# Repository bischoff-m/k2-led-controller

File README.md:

# LED Controller for K2 Bar
This app is composed of an electron app and an arduino file. The arduino controls LEDs via a custom DMX protocol and the electron app lets the user control the color and brightness of the LEDs. This application is specifically built for K2 Bar.

# Arduino Controller
Using a modified version of DmxSimple:
https://github.com/PaulStoffregen/DmxSimple

# Electron App
Use yarn instead of npm

To use electron-rebuild, setup your Visual Studio version via 
```
yarn run node-gyp configure --msvs_version=2017
```
or
```
npm config edit
```

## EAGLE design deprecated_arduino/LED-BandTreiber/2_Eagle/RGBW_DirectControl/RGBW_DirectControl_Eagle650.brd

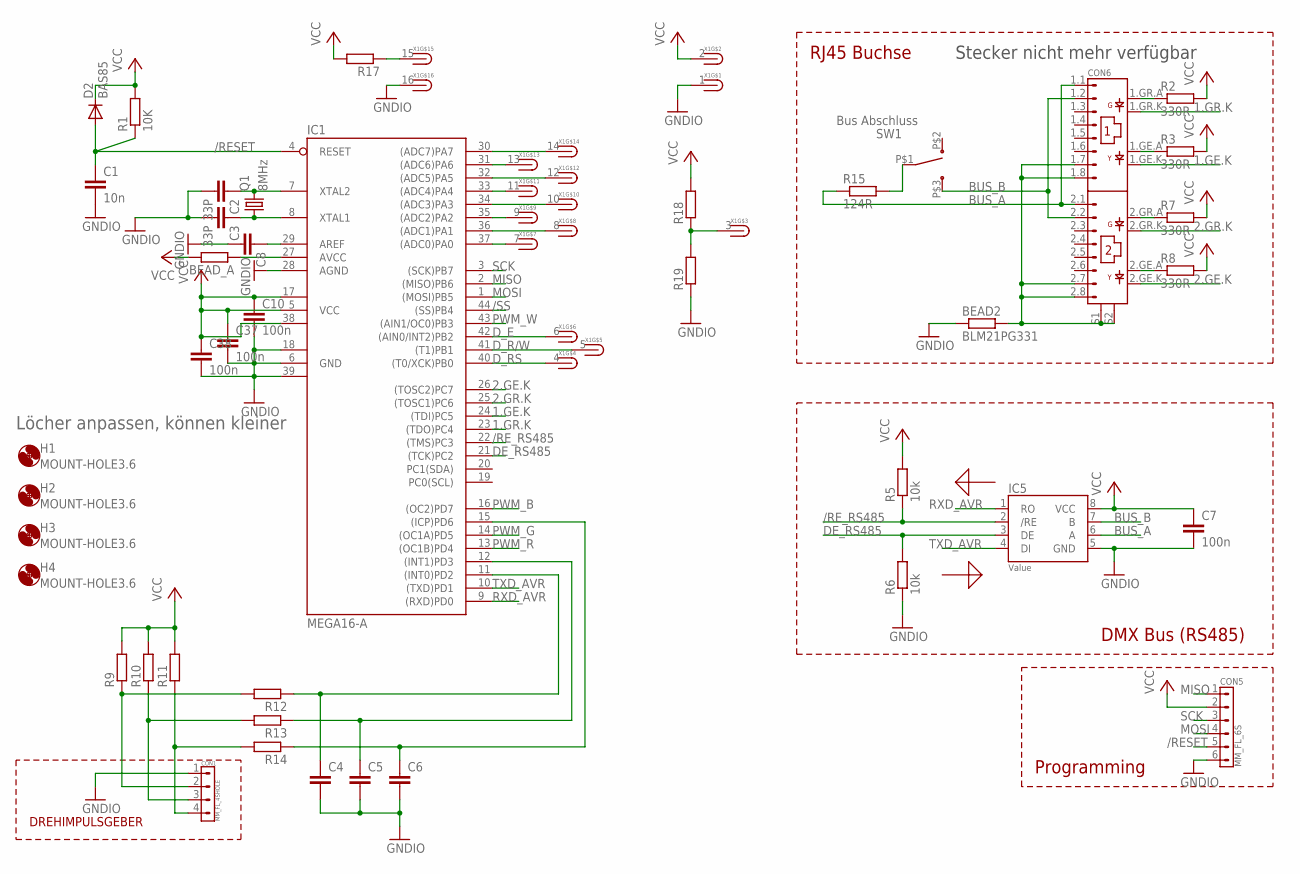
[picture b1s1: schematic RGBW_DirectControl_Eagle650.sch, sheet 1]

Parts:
BEAD2: BLM21PG331; R0805
BEAD_A: R-EU_R0805; R0805
C1: 10n; C0805
C2, C3: 33P; C0805
C4, C5, C6, C8: C-EUC0805; C0805
C7, C10, C37, C38: 100n; C0805
CON1: MM_FL_4SHOLE; MM_FL_4G
CON5: MM_FL_6S; MM_FL_6G
CON6: RJ45_2ER_LED
D2: BAS85; SOD80C
H1, H2, H3, H4: MOUNT-HOLE3.6; 3,6
IC1: MEGA16-A; TQFP44
IC5: LT1785; SO08
Q1: 8MHz; HC49/S
R1: 10K; R0805
R2, R3, R7, R8: 330R; R0805
R5, R6: 10k; R0805
R9, R10, R11, R12, R13, R14, R18, R19: R-EU_R0603; R0603
R15: 124R; R0805
R17: R-EU_R0805; R0805
SW1: SWITCH_NK236
X1: MM_FL_16GTH; MM_FL16G

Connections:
1.GE.K: CON6.1.GE.K, IC1.24 ((TDI)PC5)
1.GR.K: CON6.1.GR.K, IC1.23 ((TDO)PC4)
2.GE.K: CON6.2.GE.K, IC1.26 ((TOSC2)PC7)
2.GR.K: CON6.2.GR.K, IC1.25 ((TOSC1)PC6)
/RESET: C1.1, CON5.5, D2.A, IC1.4 (RESET), R1.1
/RE_RS485: IC1.22 ((TMS)PC3), IC5.2 (/RE), R5.1
/SS: IC1.44 ((SS)PB4)
BUS_A: CON6.1.1, CON6.2.1, IC5.6 (A), R15.1
BUS_B: CON6.1.2, CON6.2.2, IC5.7 (B), SW1.P$3 (3)
DE_RS485: IC1.21 ((TCK)PC2), IC5.3 (DE), R6.2
D_E: IC1.42 ((AIN0/INT2)PB2), X1.6
D_R/W: IC1.41 ((T1)PB1), X1.5
D_RS: IC1.40 ((T0/XCK)PB0), X1.4
GNDIO: BEAD2.1, C1.2, C2.2, C3.2, C4.2, C5.2, C6.2, C7.2, C8.2, C10.2, C37.2, C38.2, CON1.1, CON5.6, IC1.6 (GND), IC1.18 (GND1), IC1.28 (AGND), IC1.39 (GND2), IC5.5 (GND), R6.1, R19.1, X1.1, X1.16; also elsewhere on the board
MISO: CON5.1, IC1.2 ((MISO)PB6)
MOSI: CON5.4, IC1.1 ((MOSI)PB5)
unnamed: C3.1, IC1.8 (XTAL1), Q1.1
unnamed: C2.1, IC1.7 (XTAL2), Q1.2
unnamed: IC1.30 ((ADC7)PA7), X1.14
unnamed: IC1.31 ((ADC6)PA6), X1.13
unnamed: IC1.32 ((ADC5)PA5), X1.12
unnamed: IC1.33 ((ADC4)PA4), X1.11
unnamed: IC1.34 ((ADC3)PA3), X1.10
unnamed: IC1.35 ((ADC2)PA2), X1.9
unnamed: IC1.36 ((ADC1)PA1), X1.8
unnamed: IC1.37 ((ADC0)PA0), X1.7
unnamed: CON1.2, R9.1, R12.2
unnamed: BEAD2.2, CON6.1.7, CON6.1.8, CON6.2.7, CON6.2.8, CON6.S1, CON6.S2
unnamed: CON6.1.GR.A, R2.1
unnamed: CON1.3, R10.1, R13.2
unnamed: CON6.1.GE.A, R3.1
unnamed: CON1.4, R11.1, R14.2
unnamed: CON6.2.GR.A, R7.1
unnamed: C4.1, IC1.11 ((INT0)PD2), R12.1
unnamed: CON6.2.GE.A, R8.1
unnamed: C5.1, IC1.12 ((INT1)PD3), R13.1
unnamed: C6.1, IC1.15 ((ICP)PD6), R14.1
unnamed: C8.1, IC1.29 (AREF)
unnamed: BEAD_A.1, IC1.27 (AVCC)
unnamed: R18.1, R19.2, X1.3
unnamed: R17.1, X1.15
unnamed: R15.2, SW1.P$1 (1)
PWM_B: IC1.16 ((OC2)PD7); also elsewhere on the board
PWM_G: IC1.14 ((OC1A)PD5); also elsewhere on the board
PWM_R: IC1.13 ((OC1B)PD4); also elsewhere on the board
PWM_W: IC1.43 ((AIN1/OC0)PB3); also elsewhere on the board
RXD_AVR: IC1.9 ((RXD)PD0), IC5.1 (RO)
SCK: CON5.3, IC1.3 ((SCK)PB7)
TXD_AVR: IC1.10 ((TXD)PD1), IC5.4 (DI)
VCC: BEAD_A.2, C7.1, C10.1, C37.1, C38.1, CON5.2, D2.C, IC1.5 (VCC), IC1.17 (VCC1), IC1.38 (VCC2), IC5.8 (VCC), R1.2, R2.2, R3.2, R5.2, R7.2, R8.2, R9.2, R10.2, R11.2, R17.2, R18.2, X1.2; also elsewhere on the board

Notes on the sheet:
Bus Abschluss
DMX Bus (RS485)
Programming
RJ45 Buchse
Löcher anpassen, können kleiner
DREHIMPULSGEBER
Stecker nicht mehr verfügbar

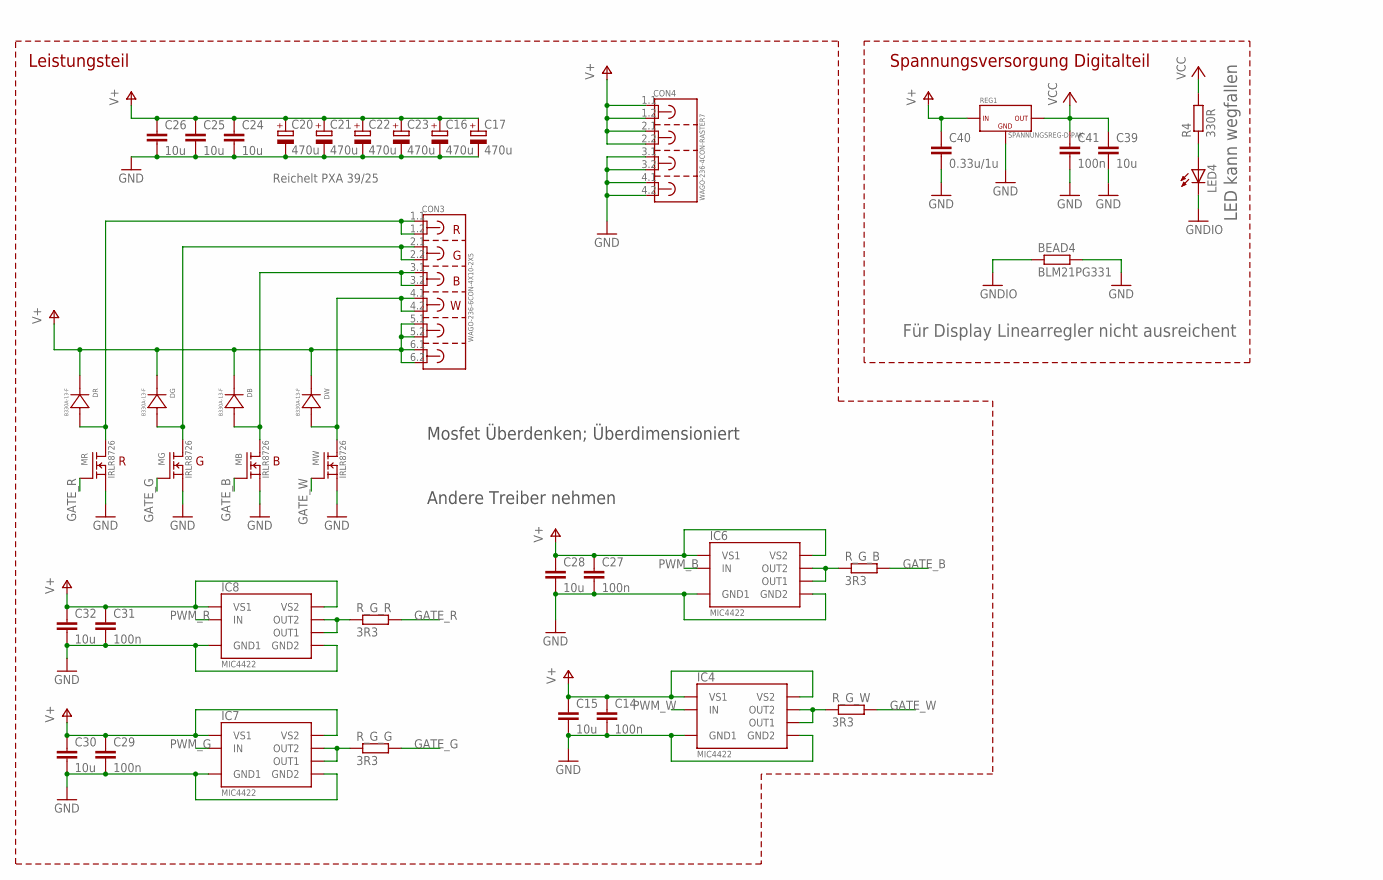
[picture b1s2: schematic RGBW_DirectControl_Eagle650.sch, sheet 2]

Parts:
BEAD4: BLM21PG331; R0805
C14, C27, C29, C31, C41: 100n; C0805
C15, C24, C25, C26, C28, C30, C32, C39: 10u; C0805
C16, C17, C20, C21, C22, C23: 470u; E5-10,5
C40: 0.33u/1u; C0805
CON3: WAGO-236-6CON-4X10-2X5; WAGO236_2X5_4X10
CON4: WAGO-236-4CON-RASTER7; WAGO236_7.5_4
DB: B330A-13-F; SMA
DG: B330A-13-F; SMA
DR: B330A-13-F; SMA
DW: B330A-13-F; SMA
IC4, IC6, IC7, IC8: MIC4422; SO08
LED4: LEDCHIP-LED0805; CHIP-LED0805
MB: IRLR8726; D-PAK
MG: IRLR8726; D-PAK
MR: IRLR8726; D-PAK
MW: IRLR8726; D-PAK
R4: 330R; R0805
REG1: SPANNUNGSREG-D-PAK; D-PAK
R_G_B: 3R3; R0805
R_G_G: 3R3; R0805
R_G_R: 3R3; R0805
R_G_W: 3R3; R0805

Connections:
GATE_B: MB.G, R_G_B.2
GATE_G: MG.G, R_G_G.2
GATE_R: MR.G, R_G_R.2
GATE_W: MW.G, R_G_W.2
GND: BEAD4.2, C14.2, C15.2, C16.-, C17.-, C20.-, C21.-, C22.-, C23.-, C24.2, C25.2, C26.2, C27.2, C28.2, C29.2, C30.2, C31.2, C32.2, C39.2, C40.2, C41.2, CON4.3.1, CON4.3.2, CON4.4.1, CON4.4.2, IC4.4 (GND1), IC4.5 (GND2), IC6.4 (GND1), IC6.5 (GND2), IC7.4 (GND1), IC7.5 (GND2), IC8.4 (GND1), IC8.5 (GND2), MB.S, MG.S, MR.S, MW.S, REG1.D (GND)
GNDIO: BEAD4.1, LED4.C; also elsewhere on the board
unnamed: LED4.A, R4.1
unnamed: IC4.6 (OUT1), IC4.7 (OUT2), R_G_W.1
unnamed: IC6.6 (OUT1), IC6.7 (OUT2), R_G_B.1
unnamed: IC8.6 (OUT1), IC8.7 (OUT2), R_G_R.1
unnamed: IC7.6 (OUT1), IC7.7 (OUT2), R_G_G.1
PHASE_B: CON3.3.1, CON3.3.2 (3.3), DB.A, MB.D
PHASE_G: CON3.2.1, CON3.2.2, DG.A, MG.D
PHASE_R: CON3.1.1, CON3.1.2, DR.A, MR.D
PHASE_W: CON3.4.1, CON3.4.2, DW.A, MW.D
PWM_B: IC6.2 (IN); also elsewhere on the board
PWM_G: IC7.2 (IN); also elsewhere on the board
PWM_R: IC8.2 (IN); also elsewhere on the board
PWM_W: IC4.2 (IN); also elsewhere on the board
V+: C14.1, C15.1, C16.+, C17.+, C20.+, C21.+, C22.+, C23.+, C24.1, C25.1, C26.1, C27.1, C28.1, C29.1, C30.1, C31.1, C32.1, C40.1, CON3.5.1, CON3.5.2, CON3.6.1, CON3.6.2, CON4.1.1, CON4.1.2, CON4.2.1, CON4.2.2, DB.K, DG.K, DR.K, DW.K, IC4.1 (VS1), IC4.8 (VS2), IC6.1 (VS1), IC6.8 (VS2), IC7.1 (VS1), IC7.8 (VS2), IC8.1 (VS1), IC8.8 (VS2), REG1.G (IN)
VCC: C39.1, C41.1, R4.2, REG1.S (OUT); also elsewhere on the board

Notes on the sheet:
Reichelt PXA 39/25
Leistungsteil
Spannungsversorgung Digitalteil
Für Display Linearregler nicht ausreichent
LED kann wegfallen
Mosfet Überdenken; Überdimensioniert
Andere Treiber nehmen

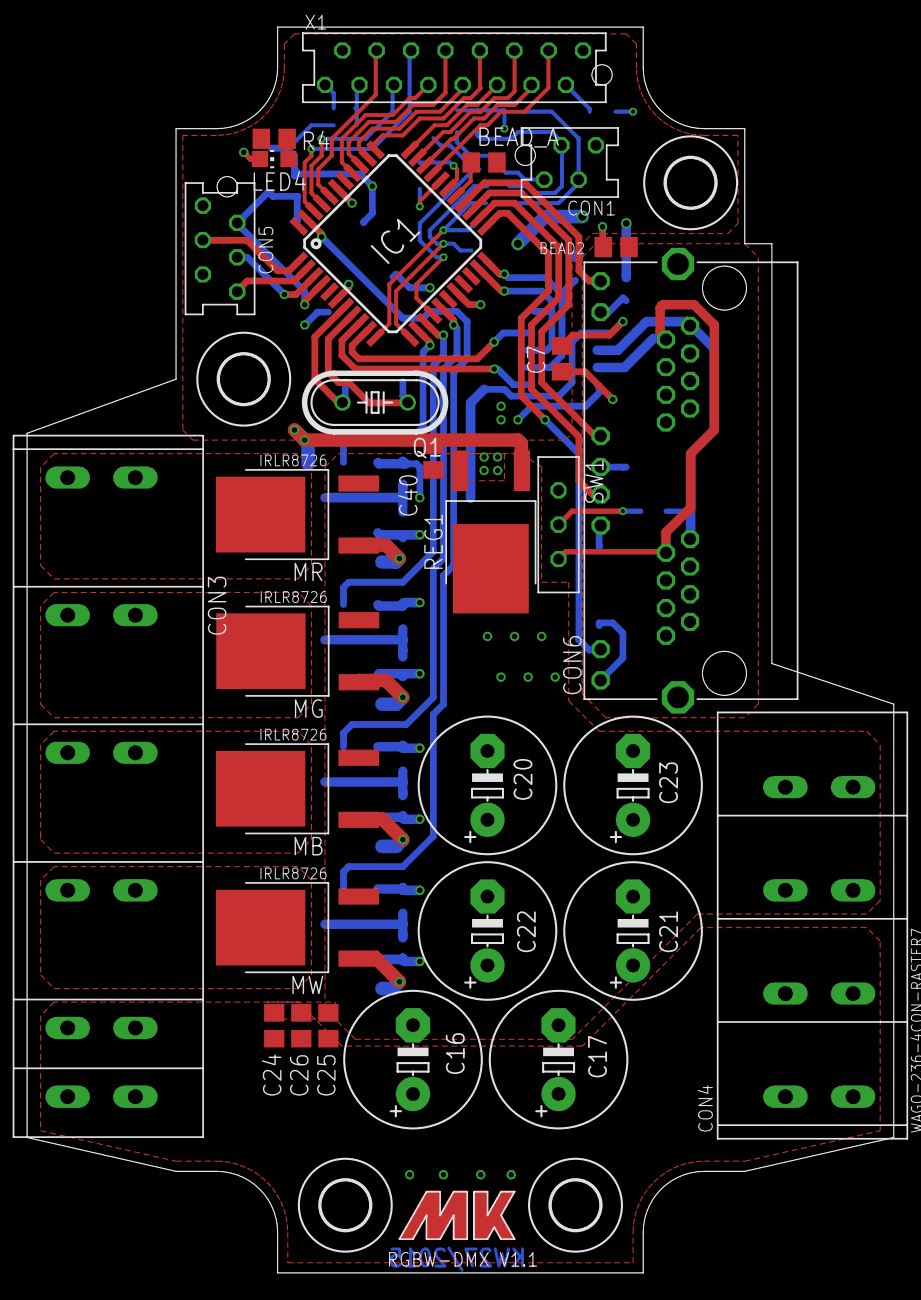
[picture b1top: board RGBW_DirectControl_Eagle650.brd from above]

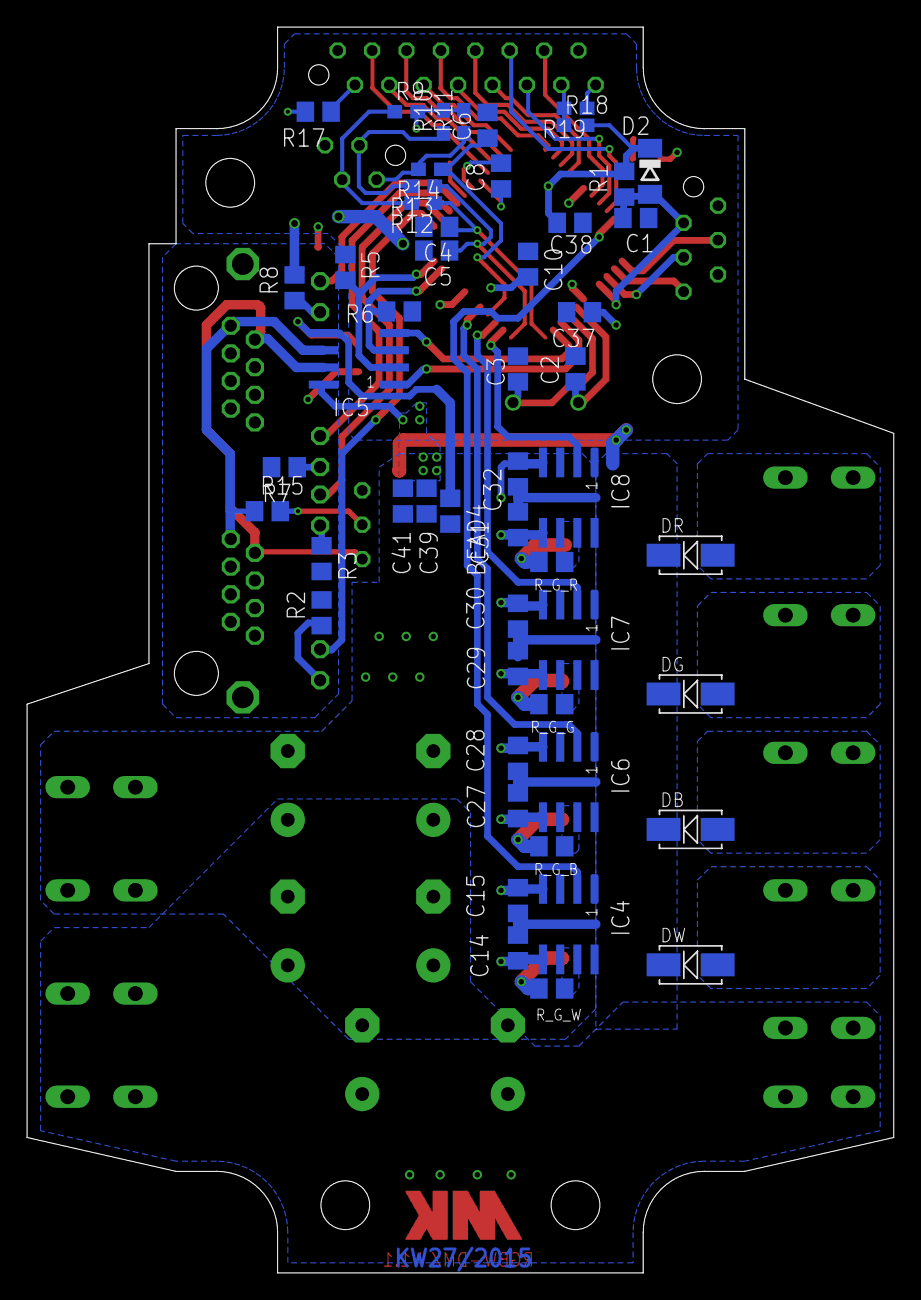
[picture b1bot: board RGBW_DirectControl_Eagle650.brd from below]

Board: 2 copper layers, 64.0 x 92.0 mm, 86 parts (52 on the bottom side), 64 nets.

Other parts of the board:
U$1: LOGO2

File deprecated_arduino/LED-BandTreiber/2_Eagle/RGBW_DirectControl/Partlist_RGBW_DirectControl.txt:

Partlist

Exported from RGBW_DirectControl_Eagle650.sch at 15.07.2015 13:27:13

EAGLE Version 6.5.0 Copyright (c) 1988-2013 CadSoft

Assembly variant: 

Part     Value                  Device                 Package          Library  Sheet

BEAD2    BLM21PG331             R-EU_R0805             R0805            rcl      1
BEAD4    BLM21PG331             R-EU_R0805             R0805            rcl      2
BEAD_A                          R-EU_R0805             R0805            rcl      1
C1       10n                    C-EUC0805              C0805            rcl      1
C2       33P                    C-EUC0805              C0805            rcl      1
C3       33P                    C-EUC0805              C0805            rcl      1
C4                              C-EUC0805              C0805            rcl      1
C5                              C-EUC0805              C0805            rcl      1
C6                              C-EUC0805              C0805            rcl      1
C7       100n                   C-EUC0805              C0805            rcl      1
C8                              C-EUC0805              C0805            rcl      1
C10      100n                   C-EUC0805              C0805            rcl      1
C14      100n                   C-EUC0805              C0805            rcl      2
C15      10u                    C-EUC0805              C0805            rcl      2
C16      470u                   CPOL-EUE5-10.5         E5-10,5          rcl      2
C17      470u                   CPOL-EUE5-10.5         E5-10,5          rcl      2
C20      470u                   CPOL-EUE5-10.5         E5-10,5          rcl      2
C21      470u                   CPOL-EUE5-10.5         E5-10,5          rcl      2
C22      470u                   CPOL-EUE5-10.5         E5-10,5          rcl      2
C23      470u                   CPOL-EUE5-10.5         E5-10,5          rcl      2
C24      10u                    C-EUC0805              C0805            rcl      2
C25      10u                    C-EUC0805              C0805            rcl      2
C26      10u                    C-EUC0805              C0805            rcl      2
C27      100n                   C-EUC0805              C0805            rcl      2
C28      10u                    C-EUC0805              C0805            rcl      2
C29      100n                   C-EUC0805              C0805            rcl      2
C30      10u                    C-EUC0805              C0805            rcl      2
C31      100n                   C-EUC0805              C0805            rcl      2
C32      10u                    C-EUC0805              C0805            rcl      2
C37      100n                   C-EUC0805              C0805            rcl      1
C38      100n                   C-EUC0805              C0805            rcl      1
C39      10u                    C-EUC0805              C0805            rcl      2
C40      0.33u/1u               C-EUC0805              C0805            rcl      2
C41      100n                   C-EUC0805              C0805            rcl      2
CON1     MM_FL_4SHOLE           MM_FL_4SHOLE           MM_FL_4G         marcus   1
CON3     WAGO-236-6CON-4X10-2X5 WAGO-236-6CON-4X10-2X5 WAGO236_2X5_4X10 marcus   2
CON4     WAGO-236-4CON-RASTER7  WAGO-236-4CON-RASTER7  WAGO236_7.5_4    marcus   2
CON5     MM_FL_6S               MM_FL_6STH             MM_FL_6G         marcus   1
CON6     RJ45_2ER_LED           RJ45_2ER_LED           RJ45_2ER_LED     marcus   1
D2       BAS85                  DIODE-SOD80C           SOD80C           diode    1
DB       B330A-13-F             B330A-13-F             SMA              marcus   2
DG       B330A-13-F             B330A-13-F             SMA              marcus   2
DR       B330A-13-F             B330A-13-F             SMA              marcus   2
DW       B330A-13-F             B330A-13-F             SMA              marcus   2
IC1      MEGA16-A               MEGA16-A               TQFP44           atmel    1
IC4      MIC4422                MIC4422                SO08             marcus   2
IC5      LT1785                 LT1785                 SO08             marcus   1
IC6      MIC4422                MIC4422                SO08             marcus   2
IC7      MIC4422                MIC4422                SO08             marcus   2
IC8      MIC4422                MIC4422                SO08             marcus   2
LED4                            LEDCHIP-LED0805        CHIP-LED0805     led      2
MB       IRLR8726               IRLR8726               D-PAK            marcus   2
MG       IRLR8726               IRLR8726               D-PAK            marcus   2
MR       IRLR8726               IRLR8726               D-PAK            marcus   2
MW       IRLR8726               IRLR8726               D-PAK            marcus   2
Q1       8MHz                   CRYTALHC49S            HC49/S           crystal  1
R1       10K                    R-EU_R0805             R0805            rcl      1
R2       330R                   R-EU_R0805             R0805            rcl      1
R3       330R                   R-EU_R0805             R0805            rcl      1
R4       330R                   R-EU_R0805             R0805            rcl      2
R5       10k                    R-EU_R0805             R0805            rcl      1
R6       10k                    R-EU_R0805             R0805            rcl      1
R7       330R                   R-EU_R0805             R0805            rcl      1
R8       330R                   R-EU_R0805             R0805            rcl      1
R9                              R-EU_R0603             R0603            rcl      1
R10                             R-EU_R0603             R0603            rcl      1
R11                             R-EU_R0603             R0603            rcl      1
R12                             R-EU_R0603             R0603            rcl      1
R13                             R-EU_R0603             R0603            rcl      1
R14                             R-EU_R0603             R0603            rcl      1
R15      124R                   R-EU_R0805             R0805            rcl      1
R17                             R-EU_R0805             R0805            rcl      1
R18                             R-EU_R0603             R0603            rcl      1
R19                             R-EU_R0603             R0603            rcl      1
REG1     SPANNUNGSREG-D-PAK     SPANNUNGSREG-D-PAK     D-PAK            marcus   2
R_G_B    3R3                    R-EU_R0805             R0805            rcl      2
R_G_G    3R3                    R-EU_R0805             R0805            rcl      2
R_G_R    3R3                    R-EU_R0805             R0805            rcl      2
R_G_W    3R3                    R-EU_R0805             R0805            rcl      2
SW1      SWITCH_NK236           SWITCH_NK236           SWITCH_NK236     marcus   1
X1       MM_FL_16GTH            MM_FL_16GTH            MM_FL16G         marcus   1

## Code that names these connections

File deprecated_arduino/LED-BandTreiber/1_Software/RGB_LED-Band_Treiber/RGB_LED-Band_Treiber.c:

/*
 * RGB_LED_Band_Treiber.c
 *
 * Created: 01.03.2013 16:00:04
 *  Author: mkn
 */ 


#include <avr/io.h>
#include <avr/interrupt.h>

//Variables***************************
unsigned char state;
unsigned char usart_selection;
unsigned char uart_data[3];
unsigned char dmx_data[512];
unsigned int channel_counter;
unsigned char i;


//Constants
const unsigned char sieben_seg[10] = {
	0xC0,	0xF9,	0xA4,	0xB0,	0x99,	0x92,	0x82,	0xF8,	0x80,	0x90
	}; // 0 to 9; MSB activate DOT	
const unsigned char UBRR_PC = 51;	// Baud 9600 for PC(USB) comunication
const unsigned char UBRR_DMX = 	1;	// Baud 250000 for DMX(RS485) comunication

//Interrupt Routinen******************

ISR(USART_RXC_vect){
	// If PWREN(=PB2) is LOW an usb cable is connected
//	if(!(PORTB & (1<<PB2))){
//		uart_data[state] =	(unsigned char)	UDR;
//		PORTA =		sieben_seg[state];
//		state =	state+1;
//		if(state > 2) {
//			state = 	0;
//		}
//		OCR1B =	uart_data[0];	// PWM Red
//		OCR1A = uart_data[1];	// PWM Green
//		OCR2 = 	uart_data[2];	// PWM Blue
//	}
//	else {
		dmx_data[channel_counter] =	UDR;
		channel_counter = channel_counter+1;
//		PORTA = 	sieben_seg[2];
//	}
}

ISR(TIMER0_COMP_vect) {
	OCR1B =	dmx_data[4];	// PWM Red
	OCR1A = dmx_data[5];	// PWM Green
	OCR2 = 	dmx_data[6];	// PWM Blue
}


//Functions***************************

void config(void){
	// Port direction
	DDRA =	(1<<PA7)|(1<<PA6)|(1<<PA5)|(1<<PA4)|(1<<PA3)|(1<<PA2)|(1<<PA1)|(1<<PA0);	//Port A Output
	
	DDRB &=		~(1<<PB2);	//Pin PB2 is input (CBUS3 of FTDI Chip; PWREN#)
	PORTB &=	~(1<<PB2);	// deactivate internal PullUp Resistor	
	
	DDRC =		(1<<PC4)|(1<<PC3)|(1<<PC2);	// /CAN_EN, /RE_RS485, DE_RS485
	PORTC =		(1<<PC4);	// activate internal PullUp for /CAN_EN. Transmitter is off by default
	
	DDRD &=		~(1<<PD3)|~(1<<PD2);	//CBUS2(TXEN) and /INT MCP2515 are inputs
	DDRD =		(1<<PD7)|(1<<PD5)|(1<<PD4); // OC2, OC1A and OC1B must be set as Output to enable PWM output driver
	PORTD &=	~(1<<PD3)|~(1<<PD2);	// disable internal PullUp Resistor
}

void pwm_config(void){
	//TC1
	// Fast PWM in non inverting mode; 8-bit bottom to top; clk/256
	TCCR1A =	(2<<COM1A0)|(2<<COM1B0)|(1<<WGM10);
	TCCR1B =	(1<<WGM12)|(4<<CS10);
	// Initialization of Output Compare Register's to 50% duty cycle
	OCR1A =		0xF0;	// =50% of 0xFF
	OCR1B =		0xF0;	// =5ß% of 0xFF
	
	//TC2
	// Fast PWM in non inverting mode; (8-bit bottom to top by default in TC2); clk/256
	TCCR2 =		(1<<WGM20)|(1<<WGM21)|(2<<COM20)|(6<<CS20);
	// Initialization of Output Compare Register
	OCR2 =		0x20;	// =50% of 0xFF
	}

void timer_conter_0_config(void) {
	// Timer Counter 0
	// CTC,clk/1024
	TCCR0 = 	(2<<WGM00)|(3<<CS00);
	TIMSK = 	(1<<OCIE0);	// Compare Inerrupt Enalbe
}
	
void uart_config(unsigned char usart_selection){
	unsigned char 	sreg;
//	sreg 	= 	SREG;		// Save Global Interrupt Flag
//	cli();					// Disable global interrupt
	// Check TXC and RXC Flag
	// Set baud rate
	if(usart_selection) {
		UBRRH = (unsigned char) (UBRR_PC>>8);
		UBRRL = (unsigned char) UBRR_PC;
		// enable receiver, enable receiver inerrupt
		UCSRB =		(1<<RXEN)|(1<<RXCIE);	
		// 1stop bit, 8 bit
		UCSRC =		(1<<URSEL)|(3<<UCSZ0);
		// disable R485 chip
		PORTC = 	(1<<PC3);	// /RE = High
		PORTC &=	~(1<<PC2); 	// DE = Low
	}
	else {
		UBRRH = (unsigned char) (UBRR_DMX>>8);
		UBRRL = (unsigned char) UBRR_DMX;
		// enable receiver, enable receiver inerrupt
		UCSRB =		(1<<RXEN)|(1<<RXCIE);	
		// 2stop bit, 8 bit
		UCSRC =		(1<<URSEL)|(1<<USBS)|(3<<UCSZ0);
		//Enable receiver mode of the RS485 chip
		PORTC &= 	~(1<<PC3)|~(1<<PC2);	// /RE and DE low

		PORTA = sieben_seg[8];
	}
//	SREG 	=	sreg;	// Restore Global Interrupt Flag
	//sei();
}

int main(void)
{
	unsigned char temp;
	config();
	pwm_config();
	uart_config(0);		// Config for DMX reception
	PORTA = 	sieben_seg[4] & ~(1<<7);
	sei();		// Global interrupt enable
//	PORTA = sieben_seg[7];
	while(1) {
//		// If PWREN(=PB2) is LOW an usb cable is connected
//		if(!(PORTB & (1<<PB2))){
//			uart_config(1);		// Config UART for communication with the PC
//		}

		// Detecting DMX Break with frame error fleg
		if (UCSRA & (1<<FE)) {
			channel_counter =	0;	// Initialize dmx channel counter
			dmx_data[0] =	UDR;	// reading UDR set the error fleg to zero
			OCR1B =	dmx_data[4];	// PWM Red
			OCR1A = dmx_data[5];	// PWM Green
			OCR2 = 	dmx_data[6];	// PWM Blue
		}
		else{
			OCR1B =		0xA0;	// Red
			OCR1A =		0x20;	// Green
			OCR2 =		0x00;;		// Blue
		}
		temp = PORTC;
		PORTA = temp;
		for(i=1;i<3;i++){
			temp = i;
		}
 	}
}

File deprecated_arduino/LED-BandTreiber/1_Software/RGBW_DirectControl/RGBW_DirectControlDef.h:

/*******************************************************

	Definitions- und Zuordnungsdatei zum

	RGBW_DirectControl Treiber 

	Marcus Knips KW47/2015


*******************************************************/

#ifndef F_CPU
#define F_CPU           8000000                   // processor clock frequency
//#warning kein F_CPU definiert
#endif

// PORT A
	#define	D0			0 	// Datenleitung 0
	#define D1			1 	// Datenleitung 1
	#define D2			2 	// Datenleitung 2
	#define D3			3 	// Datenleitung 3
	#define D4			4 	// Datenleitung 4
	#define D5			5 	// Datenleitung 5
	#define D6 			6  	// Datenleitung 6
	#define D7			7 	// Datenleitung 7
	
	#define PA_DDR		0xff	// Port A is an Output
// PORT B
	#define D_RS		0 	// Display register select
	#define D_RW		1	// Display read / write
	#define D_E			2 	// Display enable
	#define PWM_W		3	// PWM Channel white
	
	#define PB_DDR 		(1<<PWM_W)|(1<<D_E)|(1<<D_RW)|(1<<D_RS)	//output=1, input=0

// PORT C
	#define R_LED_YELLOW	7
	#define R_LED_GREEN		6
	#define L_LED_YELLOW	5
	#define L_LED_GREEN		4
	#define NRE_RS485		3	// RS485 NOT read enable
	#define DE_RS485		2	// RS485 data enable
//	#define PC_DDR			(1<<R_LED_YELLOW)|(1<<R_LED_GREEN)|(1<<L_LED_YELLOW)|(1<<L_LED_GREEN)|(1<<NRE_RS485)|(1<<DE_RS485)|(1<<TWI_SDA)|(1<<TWI_SCL)
	#define PC_DDR			0xFF	// Port C is an Output

// PORT D
	#define DA		2 		// Drehimpulsgeber Taste A
	#define DB		3		// Drehimpulsgeber Taste B
	#define TASTER	6		// Drehimpulsgeber Taster
	#define PWM_B 	7
	#define PWM_G	5
	#define PWM_R	4
	#define TXD_AVR	1
	#define RXD_AVR	0
	#define PD_DDR	(1<<PWM_B)|(1<<PWM_G)|(1<<PWM_R)|(1<<TXD_AVR)	// out=1, in=0

// Default strar condition
	#define RED_VALUE 		0xC0
	#define GREEN_VALUE		0x60
	#define BLUE_VALUE		0x00
	#define WHITE_VALUE		0xFF

	#define RED_VALUE2 		0x10
	#define GREEN_VALUE2	0x90
	#define BLUE_VALUE2		0x20
	#define WHITE_VALUE2	0xA0	

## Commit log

2020-01-21 added existing files
2020-01-21 minor bug fix
2020-01-21 updated icon
2020-01-21 added build to gitignore
2020-01-21 prepared build
2020-01-21 test
2020-01-21 added icons
2020-01-21 added check for arduino on serial port
2020-01-22 minor bug fixes
2020-04-30 Bump jquery from 3.4.1 to 3.5.0 in /electron
    Bumps [jquery](https://github.com/jquery/jquery) from 3.4.1 to 3.5.0.
    - [Release notes](https://github.com/jquery/jquery/releases)
    - [Commits](https://github.com/jquery/jquery/compare/3.4.1...3.5.0)
2020-05-01 updated dependencies
2020-05-02 initial setup for second branch
2020-06-16 modified gitignore
2020-07-29 fixed security issue
2020-07-29 fixed readme
2020-07-29 fixed minor security issue
2020-09-03 security update
2020-09-03 Bump bl from 4.0.2 to 4.0.3 in /electron
    Bumps [bl](https://github.com/rvagg/bl) from 4.0.2 to 4.0.3.
    - [Release notes](https://github.com/rvagg/bl/releases)
    - [Commits](https://github.com/rvagg/bl/compare/v4.0.2...v4.0.3)
2020-09-18 added todo
2020-09-24 Bump bl from 4.0.2 to 4.0.3 in /electron dependencies
2020-09-26 added XD design file
2020-09-27 added frequency test and increased baudrate
2020-10-02 added single comment in main.js
2020-10-02 changed comm protocol for electron and arduino
2020-10-03 integrated new protocol into frequency test bench
2020-12-12 Bump ini from 1.3.5 to 1.3.8 in /electron
    Bumps [ini](https://github.com/isaacs/ini) from 1.3.5 to 1.3.8.
    - [Release notes](https://github.com/isaacs/ini/releases)
    - [Commits](https://github.com/isaacs/ini/compare/v1.3.5...v1.3.8)
2021-01-28 Bump electron from 7.3.3 to 9.4.0 in /electron
    Bumps [electron](https://github.com/electron/electron) from 7.3.3 to 9.4.0.
    - [Release notes](https://github.com/electron/electron/releases)
    - [Changelog](https://github.com/electron/electron/blob/master/docs/breaking-changes.md)
    - [Commits](https://github.com/electron/electron/compare/v7.3.3...v9.4.0)
2021-03-31 Bump y18n from 4.0.0 to 4.0.1 in /electron
    Bumps [y18n](https://github.com/yargs/y18n) from 4.0.0 to 4.0.1.
    - [Release notes](https://github.com/yargs/y18n/releases)
    - [Changelog](https://github.com/yargs/y18n/blob/master/CHANGELOG.md)
    - [Commits](https://github.com/yargs/y18n/commits)
2021-05-09 Bump hosted-git-info from 2.8.8 to 2.8.9 in /electron
    Bumps [hosted-git-info](https://github.com/npm/hosted-git-info) from 2.8.8 to 2.8.9.
    - [Release notes](https://github.com/npm/hosted-git-info/releases)
    - [Changelog](https://github.com/npm/hosted-git-info/blob/v2.8.9/CHANGELOG.md)
    - [Commits](https://github.com/npm/hosted-git-info/compare/v2.8.8...v2.8.9)
2021-05-11 Bump lodash from 4.17.20 to 4.17.21 in /electron
    Bumps [lodash](https://github.com/lodash/lodash) from 4.17.20 to 4.17.21.
    - [Release notes](https://github.com/lodash/lodash/releases)
    - [Commits](https://github.com/lodash/lodash/compare/4.17.20...4.17.21)
2021-06-11 Bump normalize-url from 4.5.0 to 4.5.1 in /electron
    Bumps [normalize-url](https://github.com/sindresorhus/normalize-url) from 4.5.0 to 4.5.1.
    - [Release notes](https://github.com/sindresorhus/normalize-url/releases)
    - [Commits](https://github.com/sindresorhus/normalize-url/commits)
    ---
    updated-dependencies:
    - dependency-name: normalize-url
2021-08-04 Bump tar from 4.4.13 to 4.4.15 in /electron
    Bumps [tar](https://github.com/npm/node-tar) from 4.4.13 to 4.4.15.
    - [Release notes](https://github.com/npm/node-tar/releases)
    - [Changelog](https://github.com/npm/node-tar/blob/main/CHANGELOG.md)
    - [Commits](https://github.com/npm/node-tar/compare/v4.4.13...v4.4.15)
    ---
    updated-dependencies:
2021-08-12 Bump path-parse from 1.0.6 to 1.0.7 in /electron
    Bumps [path-parse](https://github.com/jbgutierrez/path-parse) from 1.0.6 to 1.0.7.
    - [Release notes](https://github.com/jbgutierrez/path-parse/releases)
    - [Commits](https://github.com/jbgutierrez/path-parse/commits/v1.0.7)
    ---
    updated-dependencies:
    - dependency-name: path-parse
2021-09-02 Bump tar from 4.4.13 to 4.4.19 in /electron
    Bumps [tar](https://github.com/npm/node-tar) from 4.4.13 to 4.4.19.
    - [Release notes](https://github.com/npm/node-tar/releases)
    - [Changelog](https://github.com/npm/node-tar/blob/main/CHANGELOG.md)
    - [Commits](https://github.com/npm/node-tar/compare/v4.4.13...v4.4.19)
    ---
    updated-dependencies:
2021-10-12 Bump electron from 7.3.3 to 11.5.0 in /electron
    Bumps [electron](https://github.com/electron/electron) from 7.3.3 to 11.5.0.
    - [Release notes](https://github.com/electron/electron/releases)
    - [Changelog](https://github.com/electron/electron/blob/main/docs/breaking-changes.md)
    - [Commits](https://github.com/electron/electron/compare/v7.3.3...v11.5.0)
    ---
    updated-dependencies:
2022-03-25 Bump electron from 7.3.3 to 13.6.6 in /electron
    Bumps [electron](https://github.com/electron/electron) from 7.3.3 to 13.6.6.
    - [Release notes](https://github.com/electron/electron/releases)
    - [Changelog](https://github.com/electron/electron/blob/main/docs/breaking-changes.md)
    - [Commits](https://github.com/electron/electron/compare/v7.3.3...v13.6.6)
    ---
    updated-dependencies:
2022-03-26 Bump minimist from 1.2.5 to 1.2.6 in /electron
    Bumps [minimist](https://github.com/substack/minimist) from 1.2.5 to 1.2.6.
    - [Release notes](https://github.com/substack/minimist/releases)
    - [Commits](https://github.com/substack/minimist/compare/1.2.5...1.2.6)
    ---
    updated-dependencies:
    - dependency-name: minimist
2022-04-19 Bump simple-get from 3.1.0 to 3.1.1 in /electron
    Bumps [simple-get](https://github.com/feross/simple-get) from 3.1.0 to 3.1.1.
    - [Release notes](https://github.com/feross/simple-get/releases)
    - [Commits](https://github.com/feross/simple-get/compare/v3.1.0...v3.1.1)
    ---
    updated-dependencies:
    - dependency-name: simple-get
2022-04-29 added documentation and minor modifications
2022-06-17 Bump electron from 13.6.6 to 15.5.5 in /electron
    Bumps [electron](https://github.com/electron/electron) from 13.6.6 to 15.5.5.
    - [Release notes](https://github.com/electron/electron/releases)
    - [Changelog](https://github.com/electron/electron/blob/main/docs/breaking-changes.md)
    - [Commits](https://github.com/electron/electron/compare/v13.6.6...v15.5.5)
    ---
    updated-dependencies:
2022-07-04 Bump ejs from 3.1.5 to 3.1.8 in /electron
    Bumps [ejs](https://github.com/mde/ejs) from 3.1.5 to 3.1.8.
    - [Release notes](https://github.com/mde/ejs/releases)
    - [Changelog](https://github.com/mde/ejs/blob/main/CHANGELOG.md)
    - [Commits](https://github.com/mde/ejs/compare/v3.1.5...v3.1.8)
    ---
    updated-dependencies:
2022-07-04 Bump async from 2.6.3 to 2.6.4 in /electron
    Bumps [async](https://github.com/caolan/async) from 2.6.3 to 2.6.4.
    - [Release notes](https://github.com/caolan/async/releases)
    - [Changelog](https://github.com/caolan/async/blob/v2.6.4/CHANGELOG.md)
    - [Commits](https://github.com/caolan/async/compare/v2.6.3...v2.6.4)
    ---
    updated-dependencies:
